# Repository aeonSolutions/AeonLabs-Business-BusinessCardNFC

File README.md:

[ ](https://discord.gg/hw3j3RwfJf)

[PCB-Prototyping-Catalogue](https://github.com/aeonSolutions/PCB-Prototyping-Catalogue)  >>  [Commercial Business](https://github.com/aeonSolutions/PCB-Prototyping-Catalogue/tree/main/Commercial%20Business)  >>  A Business Card with NFC

# A Business Card with NFC
This is my take on the Business Card designed and prototyped by Makers like [Lloann Boudin](http://twitter.com/loann_boudin) and available on Instructables here: https://www.instructables.com/PCB-Business-Card-With-NFC/
and also by Joep1986, available here: https://www.instructables.com/Digital-Business-Card-With-NFC/ and by [Dmitry Shlenkevitch](https://github.com/Dima-Shlenkevitch) here: https://github.com/Dima-Shlenkevitch/NFC-Business-Card
]

I've made some changes in particular added a copper track around the light bulb so it can be easier to protect circuitry with a transparent liquid acrylic. This business card feels better on touch when fabricated with a thickness of 0.4mm. 

<p align="center">
<strong> <a href="https://aeonsolutions.github.io/sponsor/business_card/">Interactive view of the PCB Layout</a> </strong> &nbsp;
  <strong> <a href="https://aeonsolutions.github.io/sponsor/business_card/circuit_schematic.html">Interactive view of the circuit schematic</a> </strong> <br>
 <sup>Click to view the latest revision</sup>
</p>

<br />

## Author

You can get in touch with me on my LinkedIn Profile:

#### Miguel Tomas

You can also follow my GitHub Profile to stay updated about my latest projects: 

<br>

**Hire me** <br>
See [here](https://github.com/aeonSolutions/PCB-Prototyping-Catalogue/wiki/How-to-Hire-AeonLabs) how to hire AeonLabs.

<br>

### Be supportive of my dedication and work towards technology education and buy me a cup of coffee
The PCB design Files I provide here for anyone to use are free. If you like this Smart Device or use it, please consider buying me a cup of coffee, a slice of pizza or a book to help me study, eat and think new PCB design files.

<p align="center">
    
</p>

### Make a donation on PayPal
Make a donation on PayPal and get a TAX refund*.

<p align="center">
    
</p>

### Support all these open hardware projects and become a GitHub sponsor  
Did you like any of my PCB KiCad Designs? Help and Support my open work to all by becoming a GitHub sponsor.

<p align="center">

</p>

# 

### License

Before proceeding to download any of AeonLabs software solutions for open-source development and/or PCB hardware electronics development make sure you are choosing the right license for your project. See [AeonLabs Solutions for Open Hardware & Source Development](https://github.com/aeonSolutions/PCB-Prototyping-Catalogue/wiki/AeonLabs-Solutions-for-Open-Hardware-&-Source-Development) for more information.

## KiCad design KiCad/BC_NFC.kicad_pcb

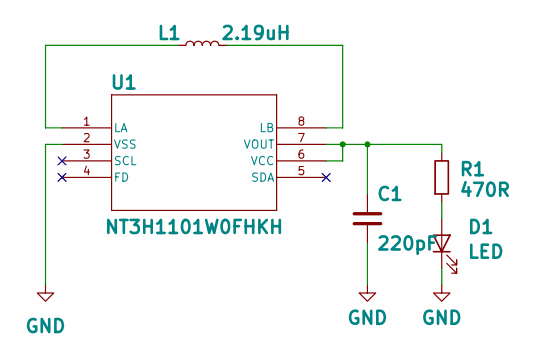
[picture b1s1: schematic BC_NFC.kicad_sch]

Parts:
C1: 220pF; C_0603_1608Metric
D1: LED; LED_0603_1608Metric
L1: 2.19uH; class4_13.56MHz
R1: 470R; R_0603_1608Metric
U1: NT3H1101W0FHKH; XQFN8_NT3H1101_NXP

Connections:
GND: C1.2, D1.1 (K), U1.2 (VSS)
unnamed: D1.2 (A), R1.2
unnamed: L1.1, U1.1 (LA)
unnamed: L1.2, U1.8 (LB)
unnamed: C1.1, R1.1, U1.6 (VCC), U1.7 (VOUT)

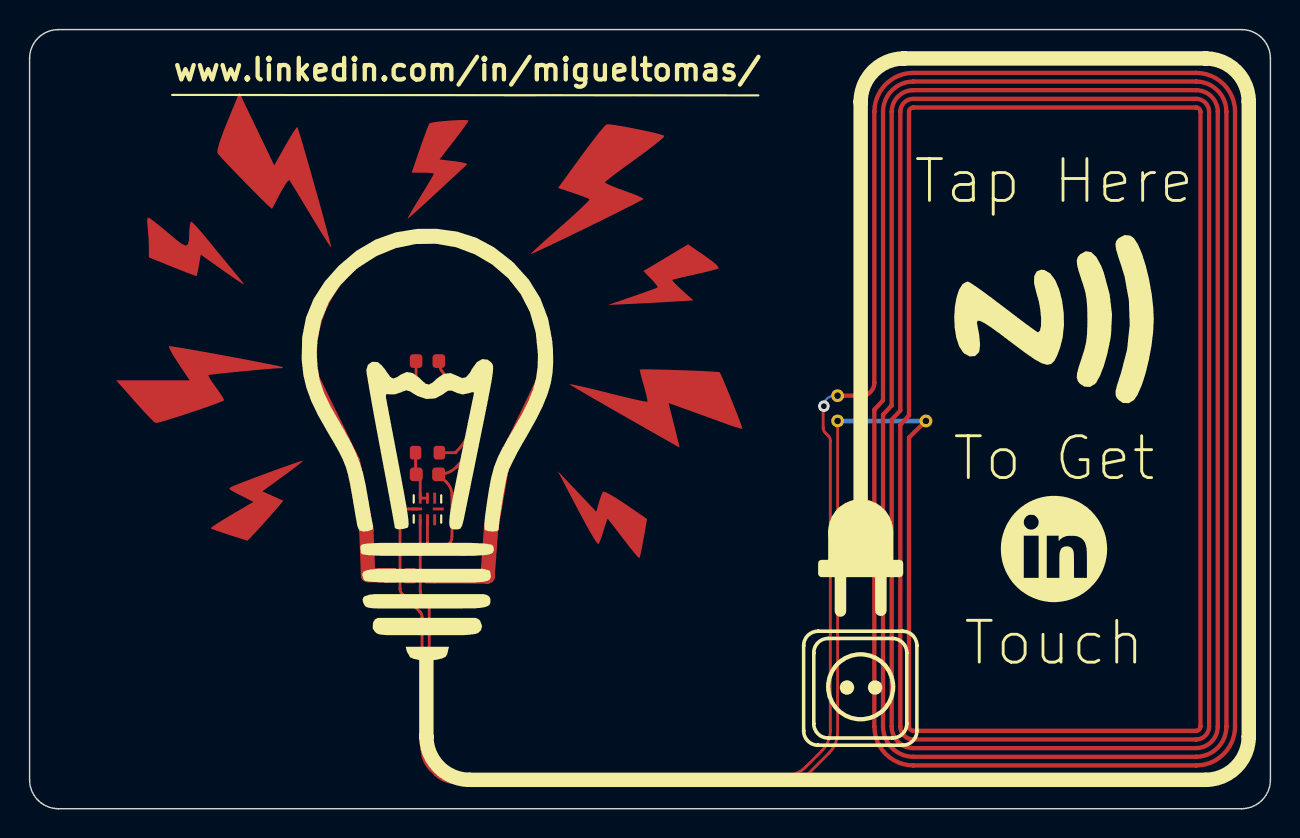
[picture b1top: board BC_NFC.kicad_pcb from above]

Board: 2 copper layers, 86.0 x 54.0 mm, 5 parts (0 on the bottom side), 5 nets.
